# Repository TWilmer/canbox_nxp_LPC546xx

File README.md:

# canbox_nxp_LPC546xx
A Project for a USB to CAN-FD and 100BaseT1 interface using a LPC546xx

This project was intially started with a cypress part, but as I was unable to source the part I swicthed to NXP. This is why there is still a cypress library in this project.

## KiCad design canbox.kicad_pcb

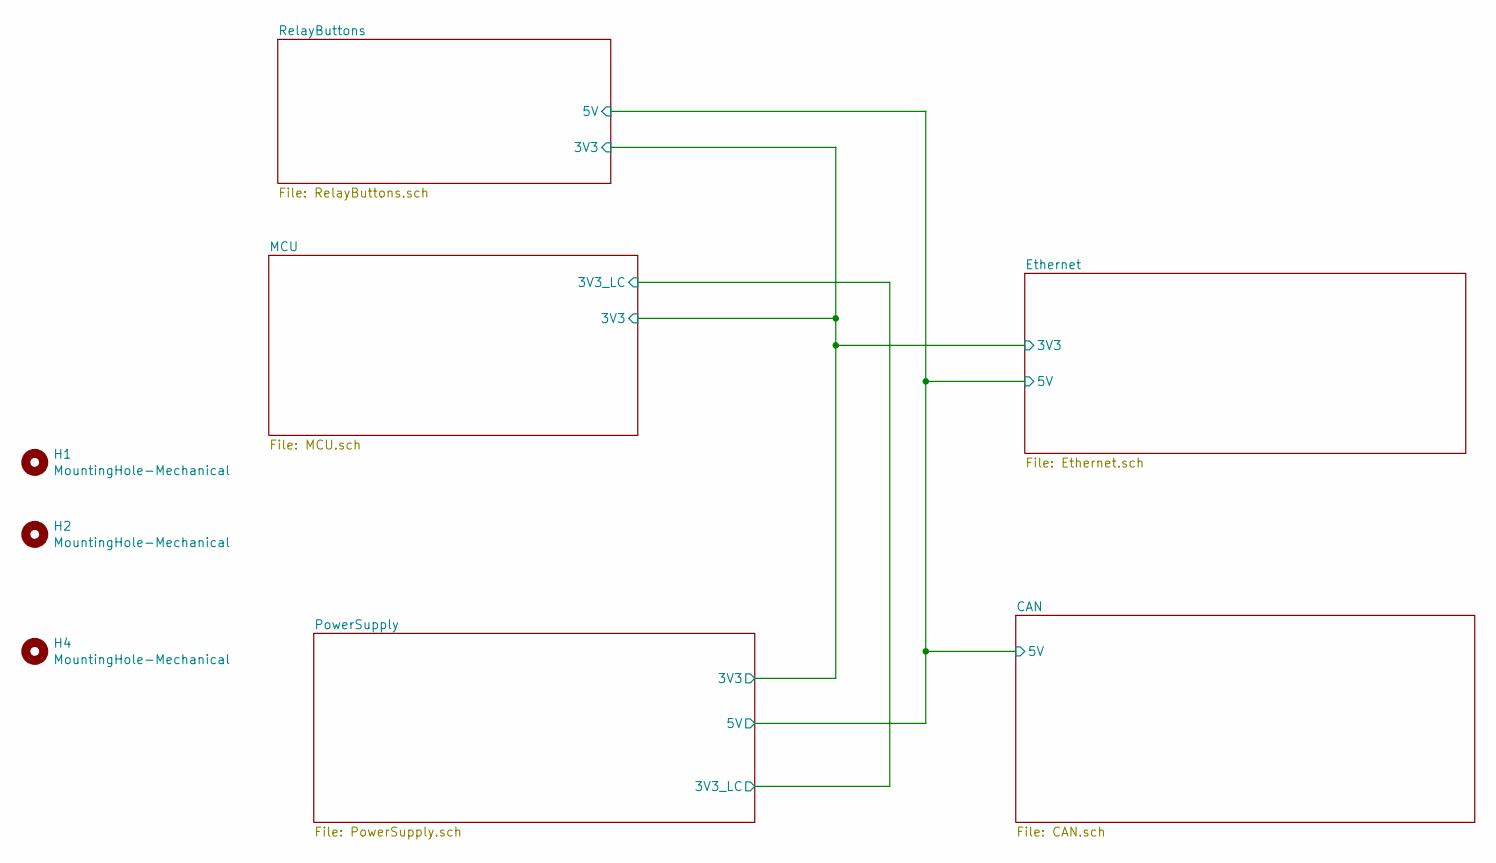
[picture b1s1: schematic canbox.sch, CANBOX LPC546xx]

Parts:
H1, H2, H4: MountingHole-Mechanical; MountingHole_2.2mm_M2_DIN965

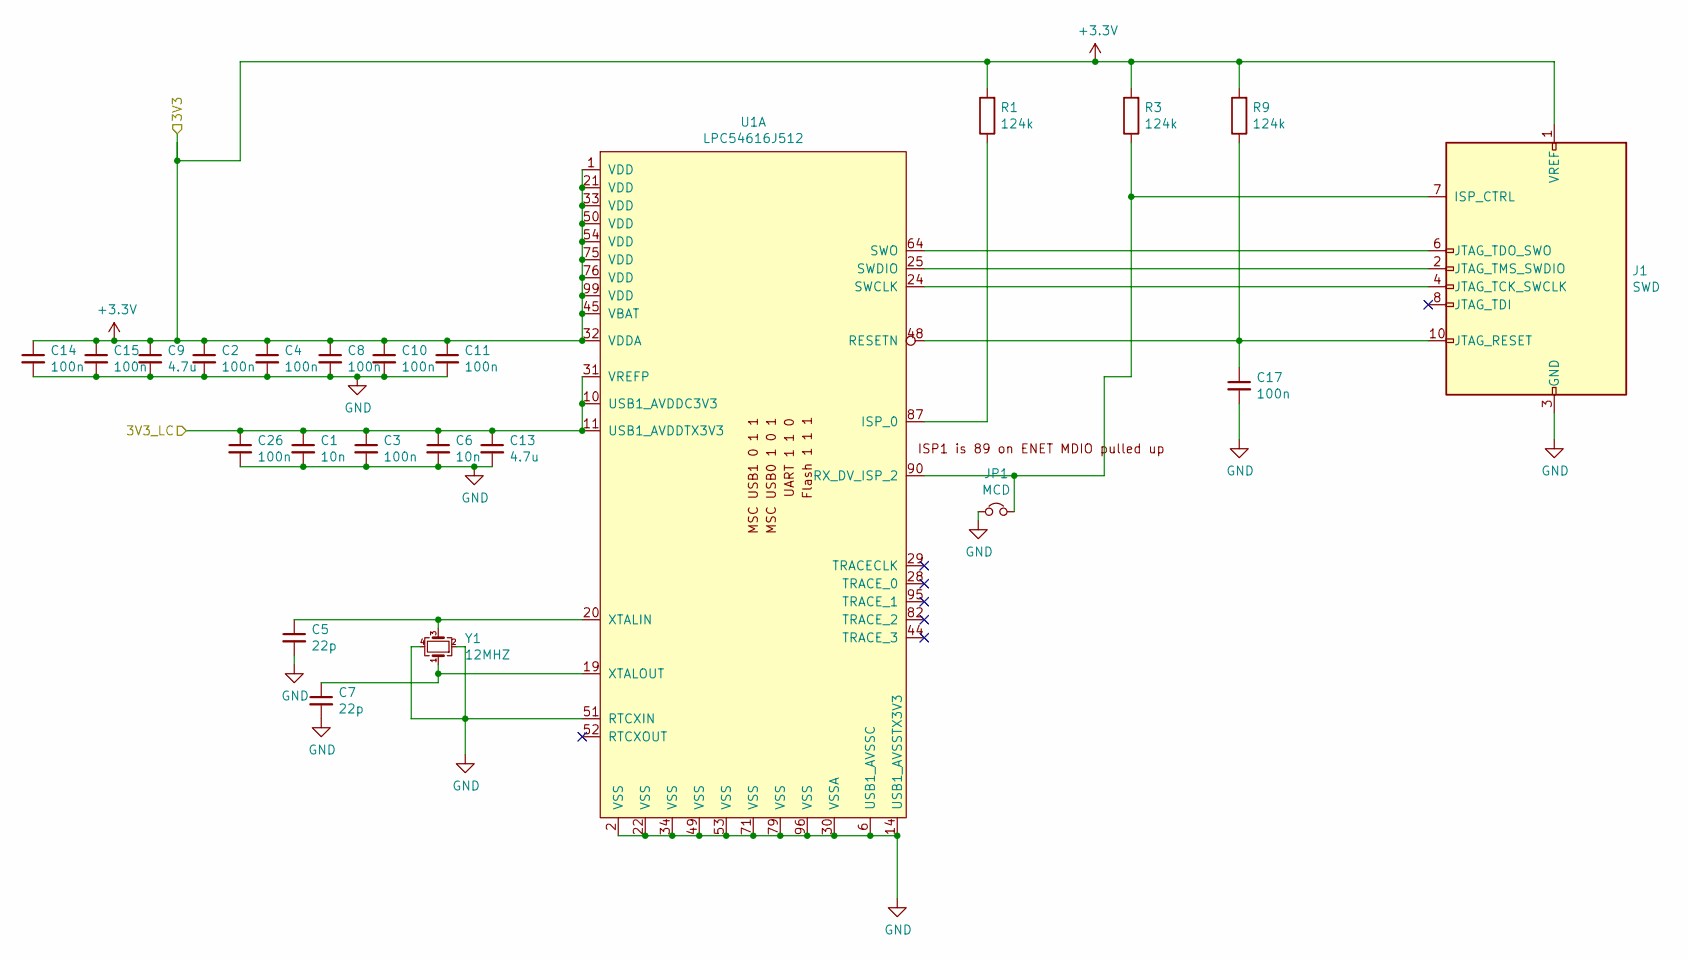
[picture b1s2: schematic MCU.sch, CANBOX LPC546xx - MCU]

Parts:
C1: 10n; C_0805_2012Metric_Pad1.15x1.40mm_HandSolder; JLC C1710
C2, C3, C4, C8, C10, C11, C14, C15, C17, C26: 100n; C_0805_2012Metric_Pad1.15x1.40mm_HandSolder; JLC C49678
C5, C7: 22p; C_0805_2012Metric_Pad1.15x1.40mm_HandSolder; JLC C1804
C6: 10n; C_0805_2012Metric_Pad1.15x1.40mm_HandSolder; JLC C1779
C9, C13: 4.7u; C_0805_2012Metric_Pad1.15x1.40mm_HandSolder; JLC C1779
J1: SWD; PinHeader_2x05_P1.27mm_Vertical_SMD
JP1: MCD; PinHeader_1x02_P2.54mm_Vertical; Mouser 22-28-4022
R1, R3, R9: 124k; R_0805_2012Metric_Pad1.15x1.40mm_HandSolder; JLC C17440
U1: LPC54616J512; LQFP-100_14x14mm_P0.5mm
Y1: 12MHZ; Crystal_SMD_3225-4Pin_3.2x2.5mm_HandSoldering; JLC C9002

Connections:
/3V3_LC: C1.1, C3.1, C6.1, C13.1, C26.1, U1.10 (USB1_AVDDC3V3), U1.11 (USB1_AVDDTX3V3), U1.31 (VREFP); also elsewhere on the board
GND: C1.2, C2.2, C3.2, C4.2, C5.2, C6.2, C7.2, C8.2, C9.2, C10.2, C11.2, C13.2, C14.2, C15.2, C17.2, C26.2, J1.3 (GND), J1.5 (GND), J1.9 (GND), JP1.1, U1.2 (VSS), U1.6 (USB1_AVSSC), U1.14 (USB1_AVSSTX3V3), U1.22 (VSS), U1.30 (VSSA), U1.34 (VSS), U1.49 (VSS), U1.51 (RTCXIN), U1.53 (VSS), U1.71 (VSS), U1.79 (VSS), U1.96 (VSS), Y1.2, Y1.4; also elsewhere on the board
unnamed: C5.1, U1.20 (XTALIN), Y1.3
unnamed: C7.1, U1.19 (XTALOUT), Y1.1
unnamed: C17.1, J1.10 (JTAG_RESET), R9.1, U1.48 (RESETN)
unnamed: J1.2 (JTAG_TMS_SWDIO), U1.25 (SWDIO)
unnamed: J1.4 (JTAG_TCK_SWCLK), U1.24 (SWCLK)
unnamed: J1.6 (JTAG_TDO_SWO), U1.64 (SWO)
unnamed: J1.7 (ISP_CTRL), JP1.2, R3.1, U1.90 (RX_DV_ISP_2)
unnamed: R1.1, U1.87 (ISP_0)

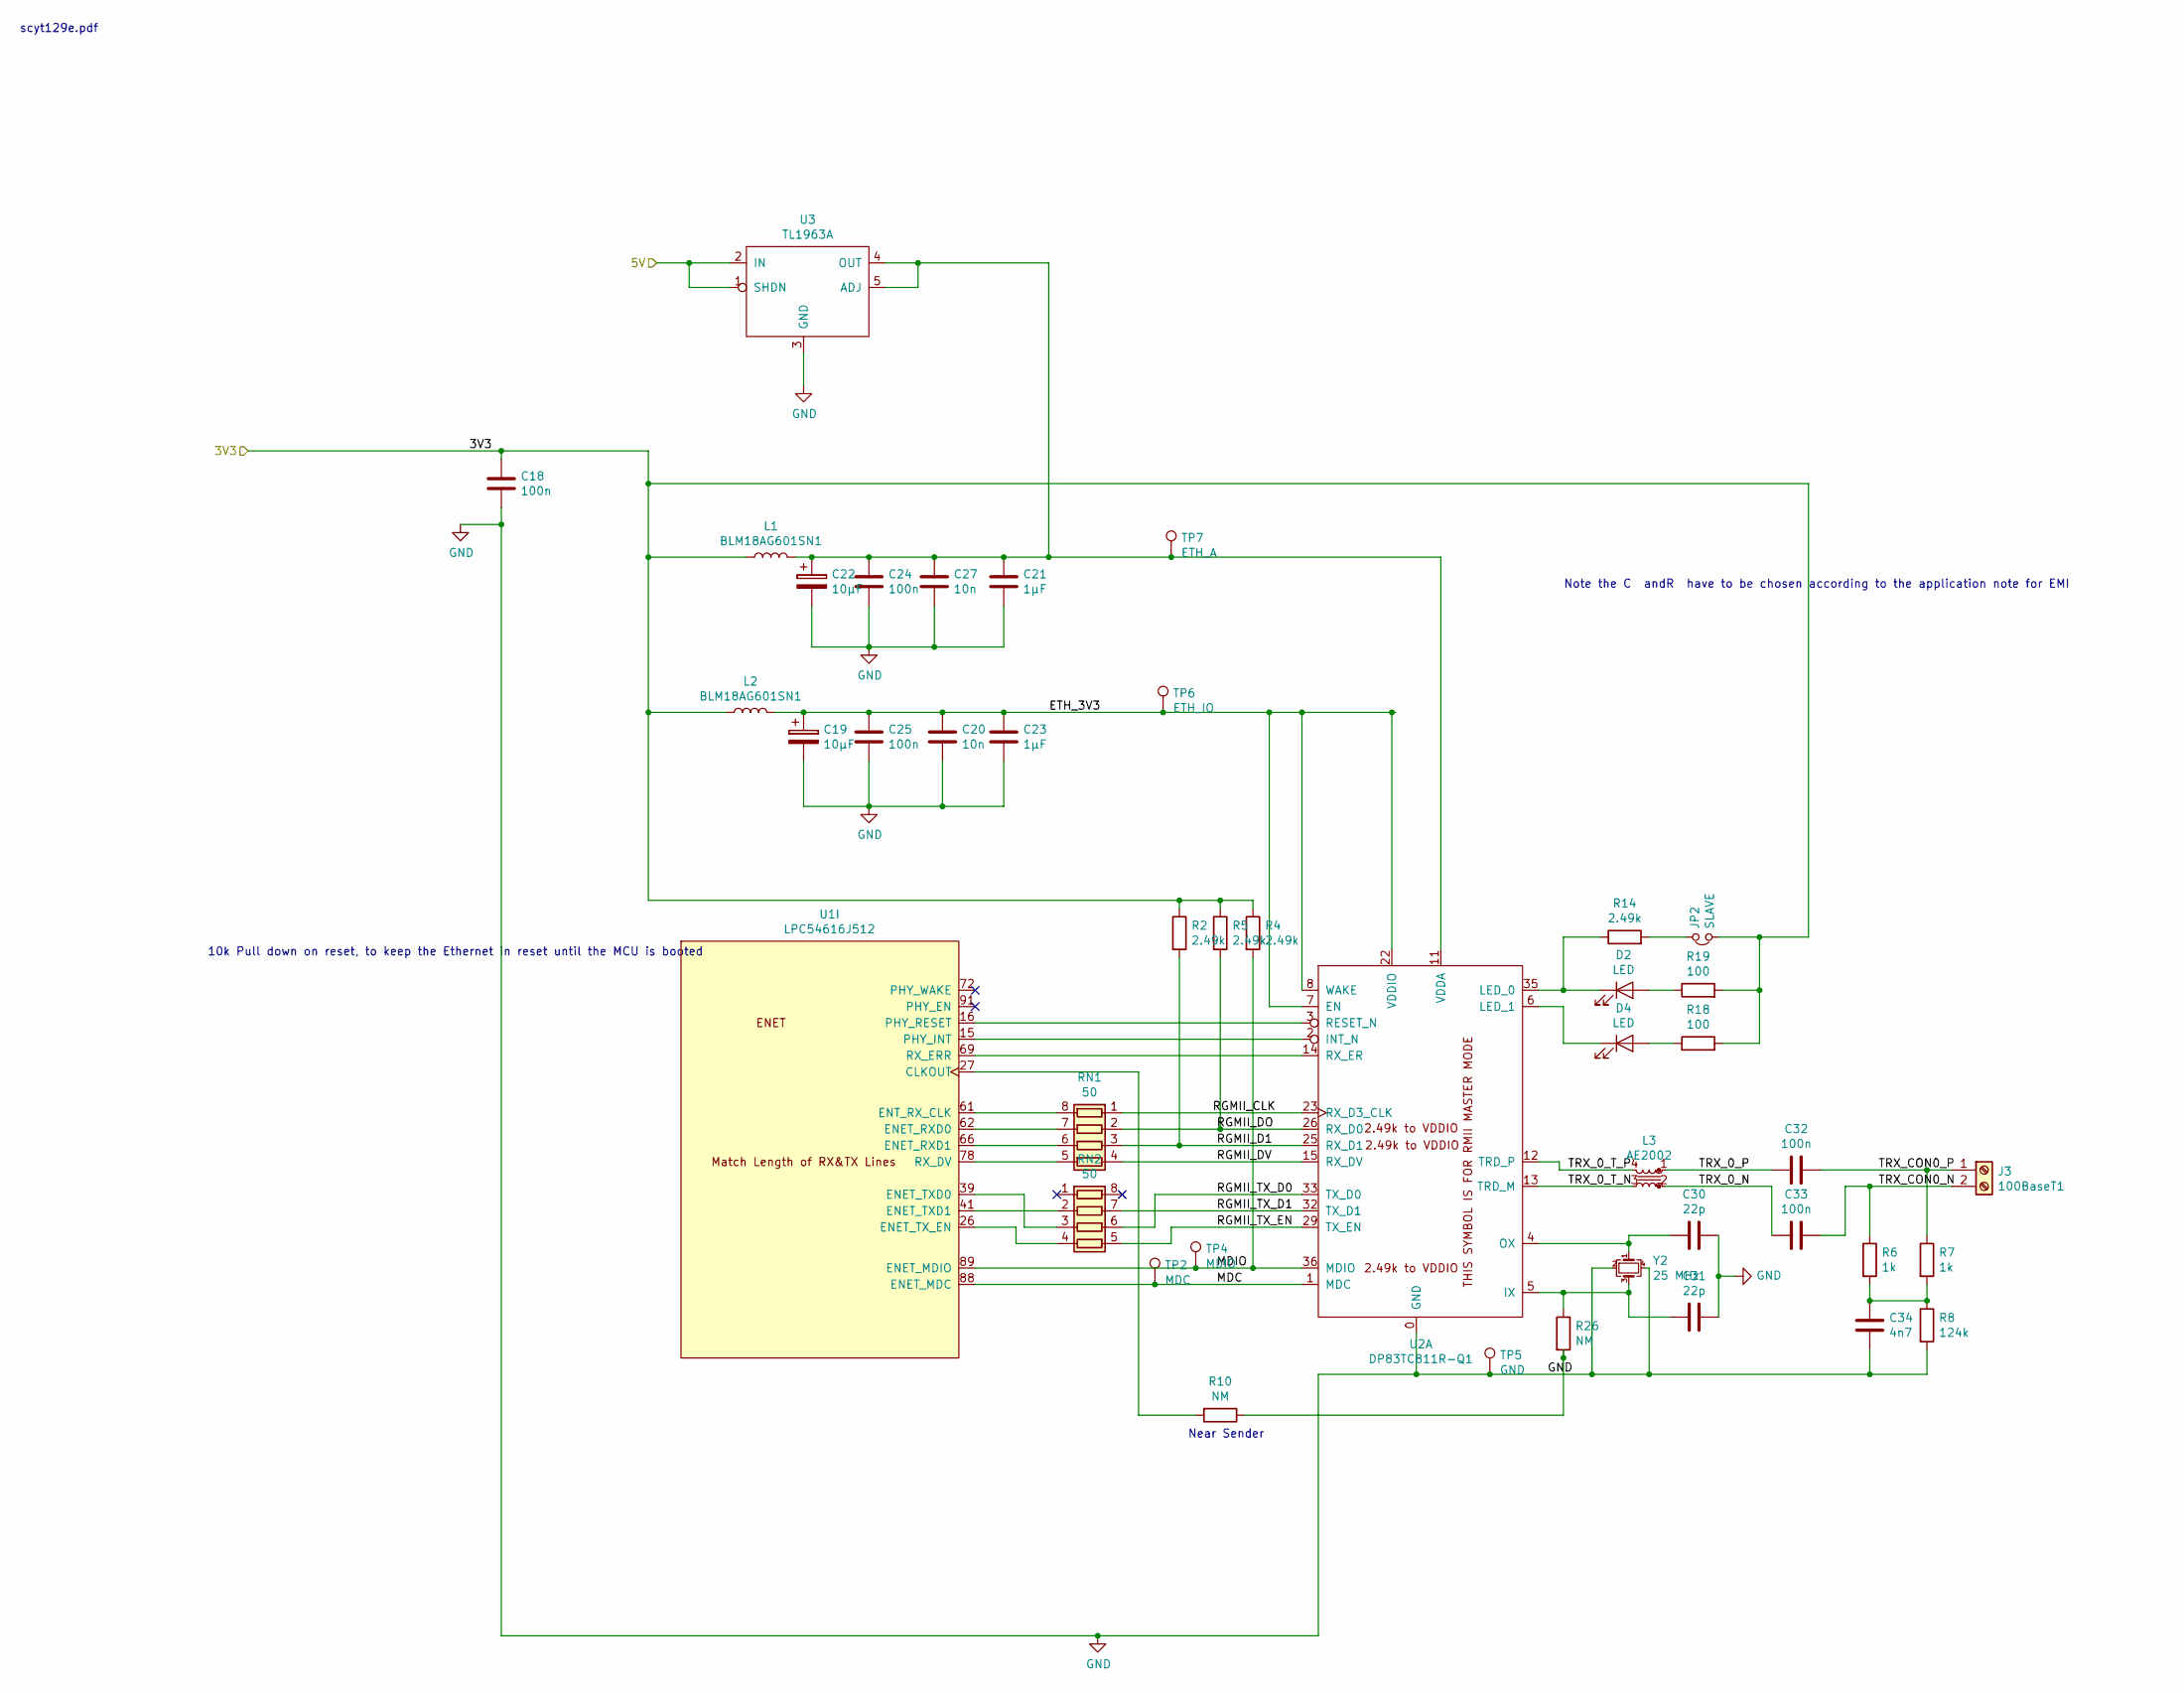
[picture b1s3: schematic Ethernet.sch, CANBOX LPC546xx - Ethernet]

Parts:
C18, C24, C25: 100n; C_0805_2012Metric_Pad1.15x1.40mm_HandSolder; JLC C49678
C19, C22: 10µF; C_0805_2012Metric_Pad1.15x1.40mm_HandSolder; JLC C45783
C20, C27: 10n; C_0805_2012Metric_Pad1.15x1.40mm_HandSolder; JLC C1710
C21, C23: 1µF; C_0805_2012Metric_Pad1.15x1.40mm_HandSolder; JLC C13967
C30, C31: 22p; C_0805_2012Metric_Pad1.15x1.40mm_HandSolder; JLC C1804
C32, C33: 100n; C_0603_1608Metric_Pad1.05x0.95mm_HandSolder; JLC C49678
C34: 4n7; C_0805_2012Metric_Pad1.15x1.40mm_HandSolder; JLC C1744
D2, D4: LED; LED_1210_3225Metric; JLC C2297
J3: 100BaseT1; TerminalBlock_Phoenix_MPT-0,5-2-2.54_1x02_P2.54mm_Horizontal; DigiKez 282834-2
JP3: SLAVE; PinHeader_1x02_P2.54mm_Vertical
L1, L2: BLM18AG601SN1; R_0603_1608Metric_Pad1.05x0.95mm_HandSolder; DigiKez 490-1014-1-ND
L3: AE2002; L_CMC_1812; DigiKez 1840-1044-1-ND
R2, R5: 2.49k; R_0402_1005Metric; Mouser ok
R4, R14: 2.49k; R_0805_2012Metric_Pad1.15x1.40mm_HandSolder; Mouser ok
R6, R7: 1k; R_0805_2012Metric_Pad1.15x1.40mm_HandSolder; Mouser ok
R8: 124k; R_0805_2012Metric_Pad1.15x1.40mm_HandSolder; JLC C17407
R10, R26: NM; R_0805_2012Metric_Pad1.15x1.40mm_HandSolder; JLC C17407
R18, R19: 100; R_0805_2012Metric_Pad1.15x1.40mm_HandSolder; Mouser ok
RN1, RN2: 50; R_Array_Concave_4x0603
TP2: MDC; TestPoint_THTPad_1.5x1.5mm_Drill0.7mm
TP4: MDIO; TestPoint_THTPad_1.5x1.5mm_Drill0.7mm
TP5: GND; TestPoint_THTPad_1.5x1.5mm_Drill0.7mm
TP6: ETH_IO; TestPoint_THTPad_1.5x1.5mm_Drill0.7mm
TP7: ETH_A; TestPoint_THTPad_1.5x1.5mm_Drill0.7mm
U1: LPC54616J512; LQFP-100_14x14mm_P0.5mm
U2: DP83TC811R-Q1; QFN-36_EP_6x6_Pitch0.5mm
U3: TL1963A; TO-263-5_TabPin3
Y2: 25 MHz; Crystal_SMD_3225-4Pin_3.2x2.5mm_HandSoldering; JLC C9006

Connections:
+5V: U3.1 (SHDN), U3.2 (IN); also elsewhere on the board
/Ethernet/ETH_3V3: C19.1, C20.1, C23.1, C25.1, L2.2, TP6.1, U2.7 (EN), U2.8 (WAKE), U2.22 (VDDIO)
/Ethernet/MDC: TP2.1, U1.88 (ENET_MDC), U2.1 (MDC)
/Ethernet/MDIO: R4.2, TP4.1, U1.89 (ENET_MDIO), U2.36 (MDIO)
/Ethernet/RGMII_CLK: RN1.1 (R1.1), U2.23 (RX_D3_CLK)
/Ethernet/RGMII_D1: R2.2, RN1.3 (R3.1), U2.25 (RX_D1)
/Ethernet/RGMII_DO: R5.2, RN1.2 (R2.1), U2.26 (RX_D0)
/Ethernet/RGMII_DV: RN1.4 (R4.1), U2.15 (RX_DV)
/Ethernet/RGMII_TX_D0: RN2.6 (R3.2), U2.33 (TX_D0)
/Ethernet/RGMII_TX_D1: RN2.7 (R2.2), U2.32 (TX_D1)
/Ethernet/RGMII_TX_EN: RN2.5 (R4.2), U2.29 (TX_EN)
/Ethernet/TRX_0_N: C33.1, L3.2
/Ethernet/TRX_0_P: C32.2, L3.1
/Ethernet/TRX_0_T_N: L3.3, U2.13 (TRD_M)
/Ethernet/TRX_0_T_P: L3.4, U2.12 (TRD_P)
/Ethernet/TRX_CON0_N: C33.2, J3.2, R6.1
/Ethernet/TRX_CON0_P: C32.1, J3.1, R7.1
GND: C18.2, C19.2, C20.2, C21.2, C22.2, C23.2, C24.2, C25.2, C27.2, C30.2, C31.2, C34.1, R8.2, TP5.1, U2.0 (GND), U3.3 (GND), Y2.2, Y2.4; also elsewhere on the board
unnamed: C21.1, C22.1, C24.1, C27.1, L1.2, TP7.1, U2.11 (VDDA), U3.4 (OUT), U3.5 (ADJ)
unnamed: C30.1, U2.4 (OX), Y2.1
unnamed: C31.1, R26.1, U2.5 (IX), Y2.3
unnamed: C34.2, R6.2, R7.2, R8.1
unnamed: D2.1 (K), R14.1, U2.35 (LED_0)
unnamed: D2.2 (A), R19.1
unnamed: D4.1 (K), U2.6 (LED_1)
unnamed: D4.2 (A), R18.1
unnamed: R10.1, R26.2
unnamed: R10.2, U1.27 (CLKOUT)
unnamed: RN1.5 (R4.2), U1.78 (RX_DV)
unnamed: RN1.6 (R3.2), U1.66 (ENET_RXD1)
unnamed: RN1.7 (R2.2), U1.62 (ENET_RXD0)
unnamed: RN1.8 (R1.2), U1.61 (ENT_RX_CLK)
unnamed: RN2.2 (R2.1), U1.41 (ENET_TXD1)
unnamed: RN2.3 (R3.1), U1.39 (ENET_TXD0)
unnamed: RN2.4 (R4.1), U1.26 (ENET_TX_EN)
unnamed: U1.15 (PHY_INT), U2.2 (INT_N)
unnamed: U1.16 (PHY_RESET), U2.3 (RESET_N)
unnamed: U1.69 (RX_ERR), U2.14 (RX_ER)

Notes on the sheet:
10k Pull down on reset, to keep the Ethernet in reset until the MCU is booted
Note the C andR have to be chosen according to the application note for EMI
scyt129e.pdf
Near Sender

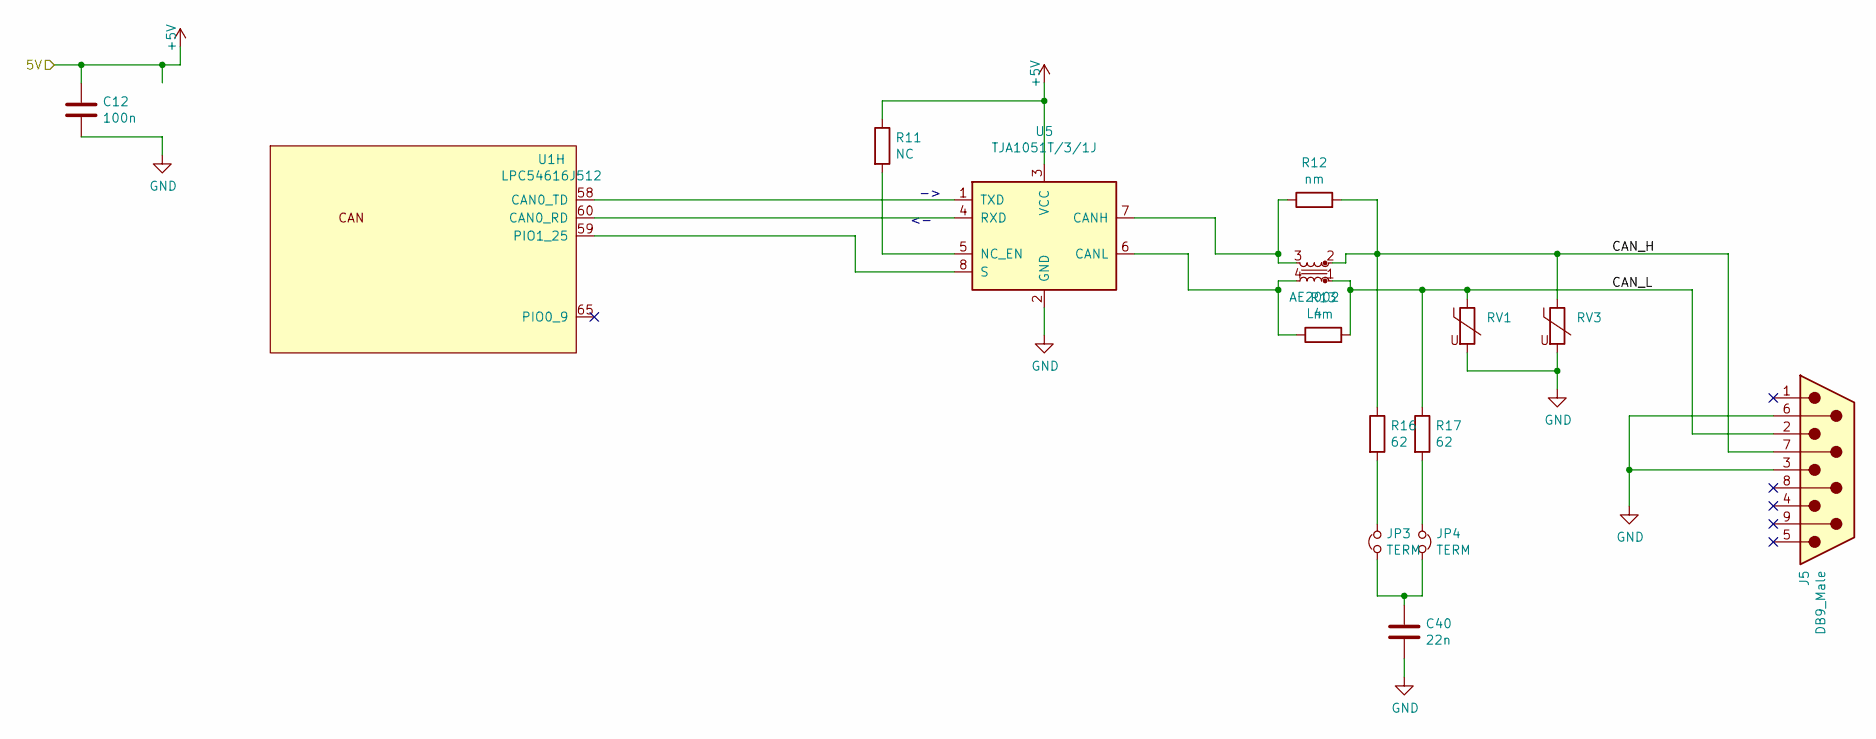
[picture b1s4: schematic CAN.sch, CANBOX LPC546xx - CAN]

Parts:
C12: 100n; C_0805_2012Metric_Pad1.15x1.40mm_HandSolder; JLC C49678
C40: 22n; C_0805_2012Metric_Pad1.15x1.40mm_HandSolder; JLC C1729
J5: DB9_Male; DSUB-9_Female_Horizontal_P2.77x2.84mm_EdgePinOffset9.90mm_H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
JP3, JP4: TERM; SolderJumper-2_P1.3mm_Open_Pad1.0x1.5mm
L4: AE2002; L_CMC_1812; DigiKez 1840-1044-1-ND
R11: NC; R_0805_2012Metric_Pad1.15x1.40mm_HandSolder
R12, R13: nm; R_0805_2012Metric_Pad1.15x1.40mm_HandSolder
R16, R17: 62; R_0805_2012Metric_Pad1.15x1.40mm_HandSolder; Mouser ok
RV1, RV3: B72510E0200K062; R_0805_2012Metric_Pad1.15x1.40mm_HandSolder; DigiKez 495-4607-1-ND
U1: LPC54616J512; LQFP-100_14x14mm_P0.5mm
U5: TJA1051T/3/1J; SOIC-8_3.9x4.9mm_P1.27mm; JLC C38695

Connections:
+5V: C12.1, R11.1, U5.3 (VCC); also elsewhere on the board
/CAN/CAN_H: J5.7, L4.2, R12.2, R16.1, RV3.1
/CAN/CAN_L: J5.2, L4.1, R13.2, R17.1, RV1.1
GND: C12.2, C40.2, J5.3, J5.6, RV1.2, RV3.2, U5.2 (GND); also elsewhere on the board
unnamed: JP4.1, R17.2
unnamed: L4.3, R12.1, U5.7 (CANH)
unnamed: L4.4, R13.1, U5.6 (CANL)
unnamed: R11.2, U5.5 (NC_EN)
unnamed: U1.58 (CAN0_TD), U5.1 (TXD)
unnamed: U1.59 (PIO1_25), U5.8 (S)
unnamed: U1.60 (CAN0_RD), U5.4 (RXD)

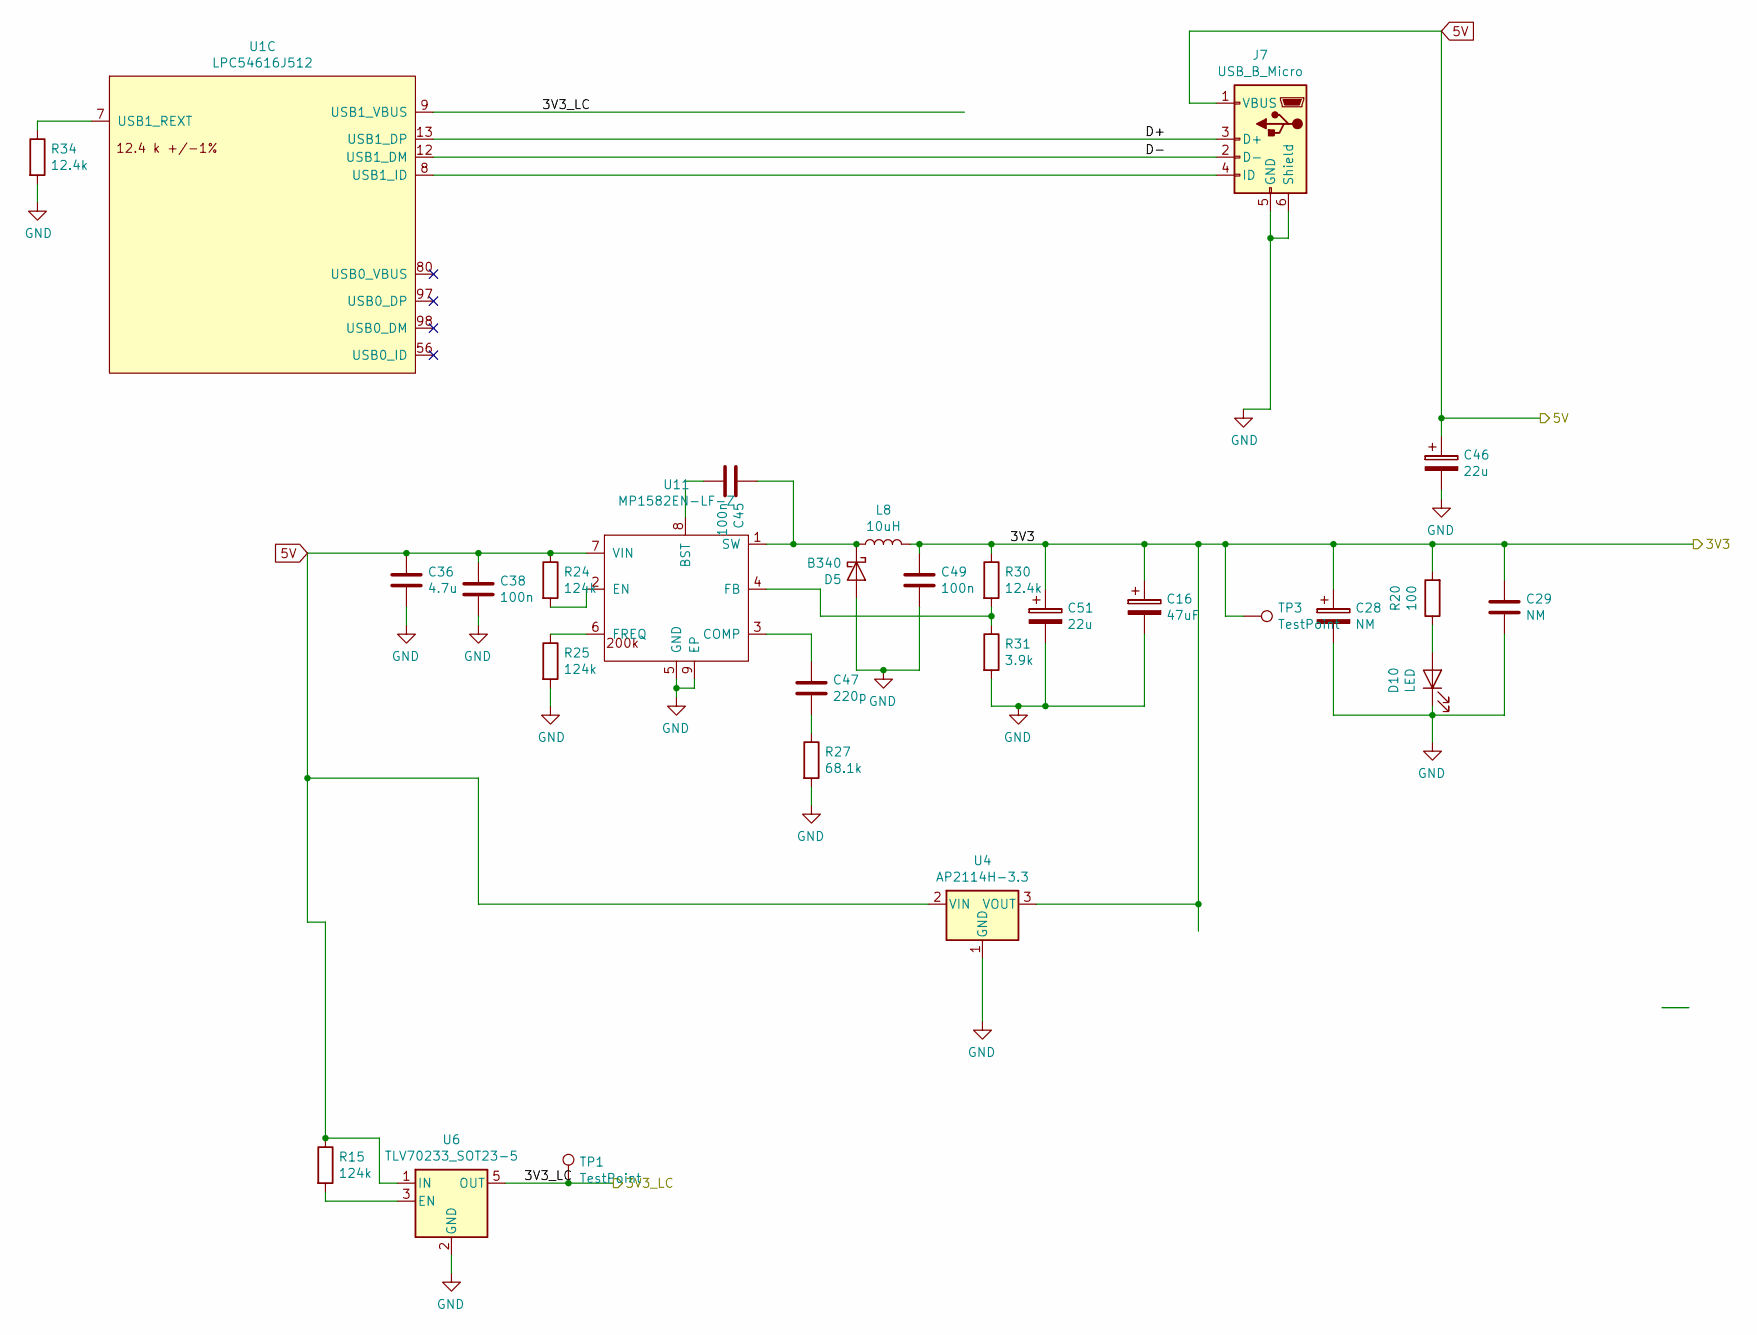
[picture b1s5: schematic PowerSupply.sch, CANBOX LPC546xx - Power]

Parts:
C16: 47uF; CP_EIA-3528-21_Kemet-B_Pad1.50x2.35mm_HandSolder; JLC C45783
C28: NM; CP_EIA-3528-21_Kemet-B_Pad1.50x2.35mm_HandSolder; JLC C45783
C29: NM; C_0805_2012Metric_Pad1.15x1.40mm_HandSolder; JLC C49678
C36: 4.7u; C_0805_2012Metric_Pad1.15x1.40mm_HandSolder; JLC C1779
C38, C45, C49: 100n; C_0805_2012Metric_Pad1.15x1.40mm_HandSolder; JLC C49678
C46: 22u; C_0805_2012Metric_Pad1.15x1.40mm_HandSolder; JLC C45783
C47: 220p; C_0805_2012Metric_Pad1.15x1.40mm_HandSolder; JLC C53172
C51: 22u; CP_EIA-3528-21_Kemet-B_Pad1.50x2.35mm_HandSolder; JLC C45783
D5: B340; D_SMB-SMC_Universal_Handsoldering; DigiKez B340AE-13
D10: LED; LED_1210_3225Metric; JLC C2297
J7: USB_B_Micro; MicroUsb
L8: 10uH; L_7.25x6.5_H3; DigiKez XC2407CT-ND
R15, R24: 124k; R_0805_2012Metric_Pad1.15x1.40mm_HandSolder; JLC C17407
R20: 100; R_0805_2012Metric_Pad1.15x1.40mm_HandSolder; Mouser ok
R25: 124k; R_0805_2012Metric_Pad1.15x1.40mm_HandSolder; Mouser ok
R27: 68.1k; R_0805_2012Metric_Pad1.15x1.40mm_HandSolder; Mouser ok
R30, R34: 12.4k; R_0805_2012Metric_Pad1.15x1.40mm_HandSolder; Mouser ok
R31: 3.9k; R_0805_2012Metric_Pad1.15x1.40mm_HandSolder; Mouser ok
TP1, TP3: TestPoint; TestPoint_THTPad_1.5x1.5mm_Drill0.7mm
U1: LPC54616J512
U4: AP2114H-3.3; SOT-223-3_TabPin2
U6: TLV70233_SOT23-5; SOT-23-5; JLC C26833
U11: MP1582EN-LF-Z; SOIC-8-1EP_3.9x4.9mm_P1.27mm_EP2.35x2.35mm; JLC C15051

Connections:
+5V: C36.1, C38.1, C46.1, J7.1 (VBUS), R15.1, R24.1, U4.2 (VIN), U6.1 (IN), U11.7 (VIN); also elsewhere on the board
/3V3_LC: TP1.1, U1.9 (USB1_VBUS), U6.5 (OUT); also elsewhere on the board
/PowerSupply/D+: J7.3 (D+), U1.13 (USB1_DP)
/PowerSupply/D-: J7.2 (D-), U1.12 (USB1_DM)
GND: C16.2, C28.2, C29.2, C36.2, C38.2, C46.2, C49.2, C51.2, D5.2 (A), D10.1 (K), J7.5 (GND), J7.6 (Shield), R25.2, R27.2, R31.2, R34.2, U4.1 (GND), U6.2 (GND), U11.5 (GND), U11.9 (EP); also elsewhere on the board
unnamed: C45.1, D5.1 (K), L8.1, U11.1 (SW)
unnamed: C45.2, U11.8 (BST)
unnamed: C47.1, U11.3 (COMP)
unnamed: C47.2, R27.1
unnamed: D10.2 (A), R20.1
unnamed: J7.4 (ID), U1.8 (USB1_ID)
unnamed: R15.2, U6.3 (EN)
unnamed: R24.2, U11.2 (EN)
unnamed: R25.1, U11.6 (FREQ)
unnamed: R30.2, R31.1, U11.4 (FB)
unnamed: R34.1, U1.7 (USB1_REXT)

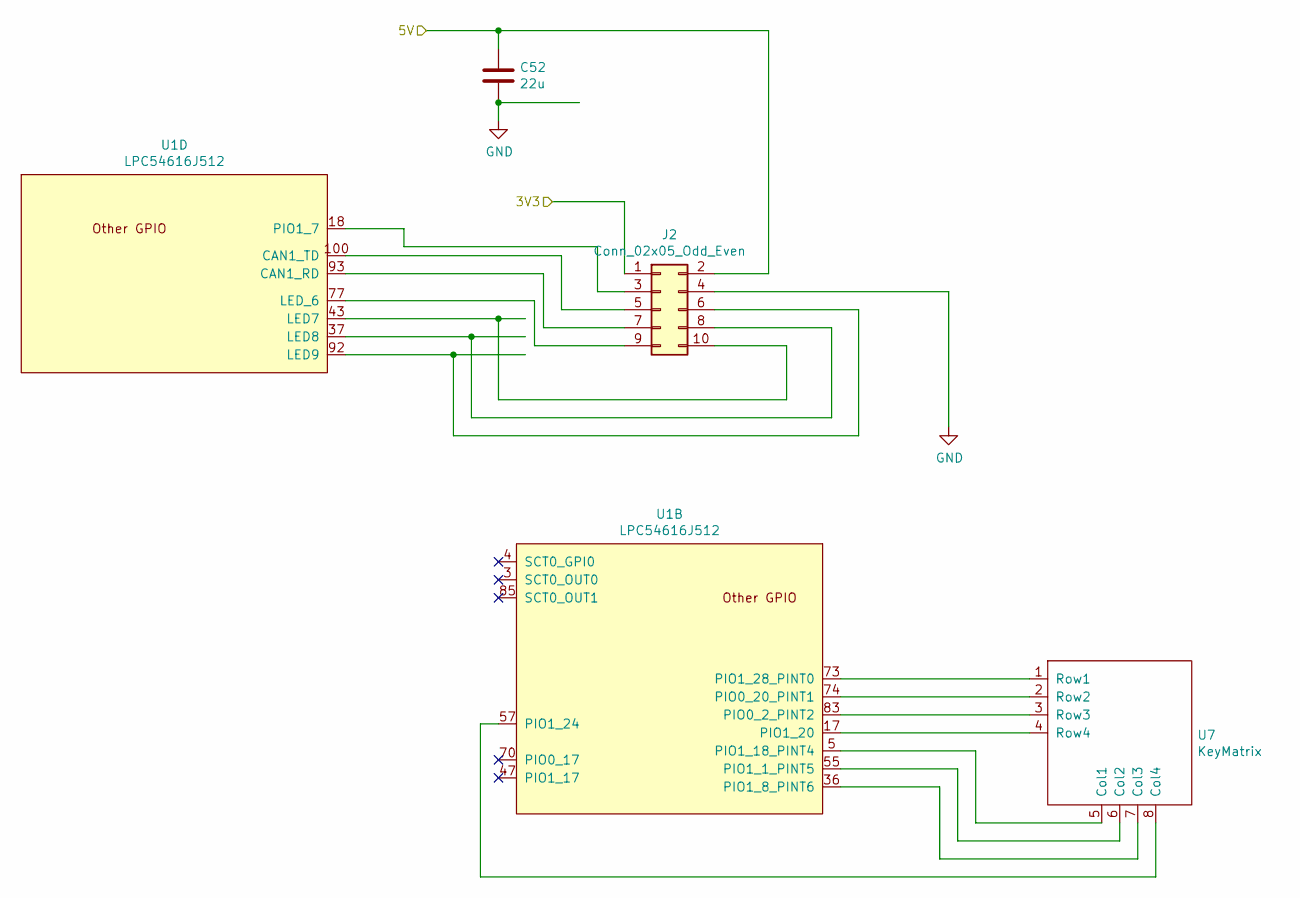
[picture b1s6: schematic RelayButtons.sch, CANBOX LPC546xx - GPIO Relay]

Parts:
C52: 22u; C_0805_2012Metric_Pad1.15x1.40mm_HandSolder; JLC C45783
J2: Conn_02x05_Odd_Even; PinHeader_2x05_P1.27mm_Vertical_SMD
U1: LPC54616J512
U7: KeyMatrix; PinHeader_1x08_P2.54mm_Vertical

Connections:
+5V: C52.1, J2.2; also elsewhere on the board
GND: C52.2, J2.4; also elsewhere on the board
unnamed: J2.3, U1.18 (PIO1_7)
unnamed: J2.5, U1.100 (CAN1_TD)
unnamed: J2.6, U1.92 (LED9)
unnamed: J2.7, U1.93 (CAN1_RD)
unnamed: J2.8, U1.37 (LED8)
unnamed: J2.9, U1.77 (LED_6)
unnamed: J2.10, U1.43 (LED7)
unnamed: U1.5 (PIO1_18_PINT4), U7.5 (Col1)
unnamed: U1.17 (PIO1_20), U7.4 (Row4)
unnamed: U1.36 (PIO1_8_PINT6), U7.7 (Col3)
unnamed: U1.55 (PIO1_1_PINT5), U7.6 (Col2)
unnamed: U1.57 (PIO1_24), U7.8 (Col4)
unnamed: U1.73 (PIO1_28_PINT0), U7.1 (Row1)
unnamed: U1.74 (PIO0_20_PINT1), U7.2 (Row2)
unnamed: U1.83 (PIO0_2_PINT2), U7.3 (Row3)

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
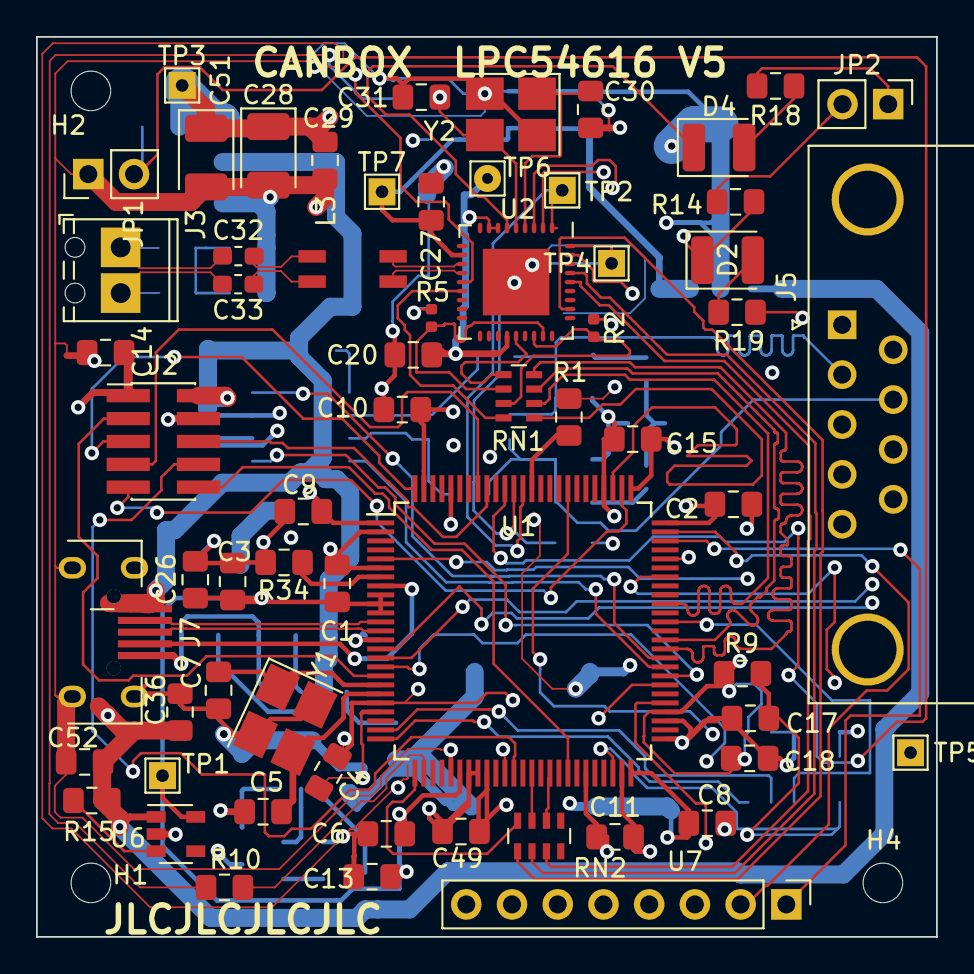
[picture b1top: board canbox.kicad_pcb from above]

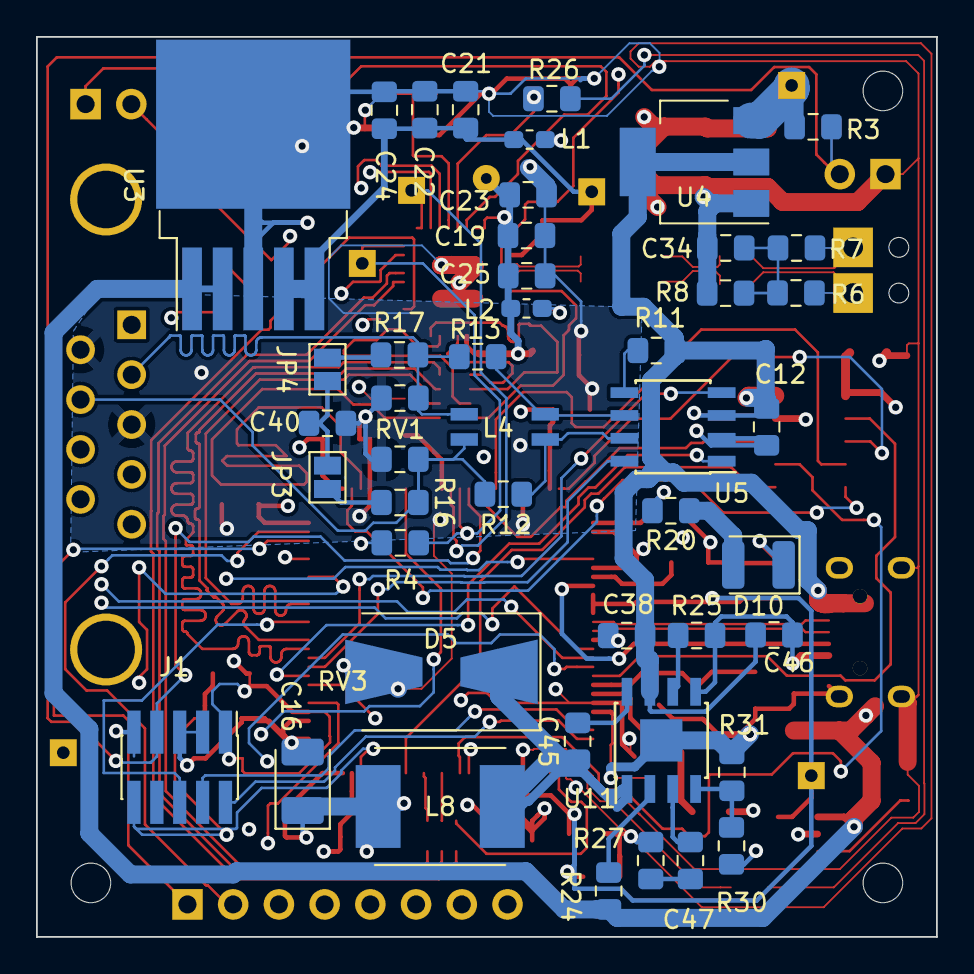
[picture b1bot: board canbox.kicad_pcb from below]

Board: 4 copper layers, 50.0 x 50.0 mm, 112 parts (46 on the bottom side), 88 nets.

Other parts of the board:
JP2: SLAVE; PinHeader_1x02_P2.54mm_Vertical

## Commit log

2019-06-02 PCB Review
2019-06-02 Update README.md
    Explain why there is a cypress library
2019-06-09 Fix few bugs, review design
2019-06-22 Add solder jumper for termination.
2019-06-22 Add batch-1 production files
2019-11-12 V3 bigger board, RMII instrumentation, inverter
2019-11-17 Improve PCB, local loopback works - via RMII not
2019-11-17 V4 PCB Release
2019-12-12 Switch to 4 Layer PCB as the RMII loopback doesn't work
2019-12-19 V5 now impedance controlled
2020-01-01 First firmware skeleton
2020-01-01 First shot linux driver
